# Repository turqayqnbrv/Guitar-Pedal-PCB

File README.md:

# Guitar-Pedal-PCB
This is a project repository for distortion pedal desgined with KiCAD

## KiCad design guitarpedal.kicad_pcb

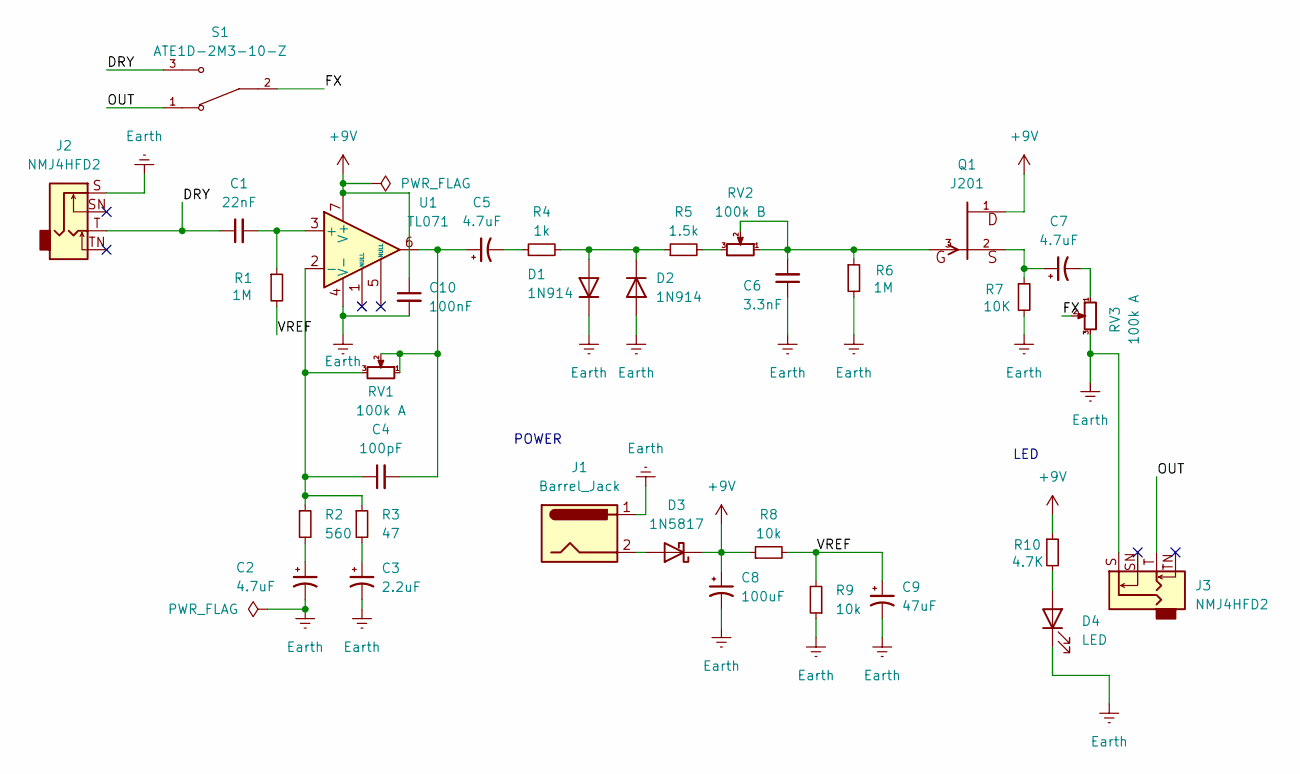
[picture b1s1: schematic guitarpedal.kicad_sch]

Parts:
C1: 22nF; C_Rect_L7.2mm_W2.5mm_P5.00mm_FKS2_FKP2_MKS2_MKP2
C2, C5, C7: 4.7uF; C_Radial_D5.0mm_H7.0mm_P2.00mm
C3: 2.2uF; C_Radial_D5.0mm_H7.0mm_P2.00mm
C4: 100pF; C_Disc_D5.0mm_W2.5mm_P5.00mm
C6: 3.3nF; C_Rect_L7.2mm_W2.5mm_P5.00mm_FKS2_FKP2_MKS2_MKP2
C8: 100uF; C_Radial_D6.3mm_H7.0mm_P2.50mm
C9: 47uF; C_Radial_D5.0mm_H7.0mm_P2.00mm
C10: 100nF; C_Disc_D5.0mm_W2.5mm_P5.00mm
D1, D2: 1N914; D_DO-35_SOD27_P7.62mm_Horizontal
D3: 1N5817; D_DO-41_SOD81_P10.16mm_Horizontal
D4: LED; LED_D5.0mm
J1: Barrel_Jack; BarrelJack_Horizontal
J2, J3: NMJ4HFD2; Jack_6.35mm_Neutrik_NMJ4HFD2_Horizontal
Q1: J201; TO-92L_Inline_Wide; MPN J201
R1, R6: 1M; R_Axial_DIN0207_L6.3mm_D2.5mm_P7.62mm_Horizontal
R2: 560; R_Axial_DIN0207_L6.3mm_D2.5mm_P7.62mm_Horizontal
R3: 47; R_Axial_DIN0207_L6.3mm_D2.5mm_P7.62mm_Horizontal
R4: 1k; R_Axial_DIN0207_L6.3mm_D2.5mm_P7.62mm_Horizontal
R5: 1.5k; R_Axial_DIN0207_L6.3mm_D2.5mm_P7.62mm_Horizontal
R7: 10K; R_Axial_DIN0207_L6.3mm_D2.5mm_P7.62mm_Horizontal
R8, R9: 10k; R_Axial_DIN0207_L6.3mm_D2.5mm_P7.62mm_Horizontal
R10: 4.7K; R_Axial_DIN0207_L6.3mm_D2.5mm_P7.62mm_Horizontal
RV1, RV3: 100k A; Potentiometer_Alps_RK163_Single_Horizontal
RV2: 100k B; Potentiometer_Alps_RK163_Single_Horizontal
S1: ATE1D-2M3-10-Z; SW_ATE1D-2M3-10-Z; MPN ATE1D-2M3-10-Z
U1: TL071; DIP-8_W7.62mm

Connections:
+9V: C8.1, C10.1, D3.1 (K), Q1.1, R8.1, R10.1, U1.7 (V+)
/DRY: C1.1, J2.T, S1.3
/FX: RV3.2, S1.2
/OUT: J3.T, S1.1
/VREF: C9.1, R1.2, R8.2, R9.2
Earth: C2.2, C3.2, C6.1, C8.2, C9.2, C10.2, D1.1 (K), D2.2 (A), D4.1 (K), J1.1, J2.S, J3.S, R6.2, R7.2, R9.1, RV3.3, U1.4 (V-)
unnamed: C2.1, R2.2
unnamed: C3.1, R3.2
unnamed: C4.2, C5.1, RV1.1, RV1.2, U1.6
unnamed: C5.2, R4.1
unnamed: C6.2, Q1.3, R6.1, RV2.1, RV2.2
unnamed: C7.1, Q1.2, R7.1
unnamed: C7.2, RV3.1
unnamed: D1.2 (A), D2.1 (K), R4.2, R5.1
unnamed: D3.2 (A), J1.2
unnamed: D4.2 (A), R10.2
unnamed: R5.2, RV2.3
unnamed: C1.2, R1.1, U1.3 (+)
unnamed: C4.1, R2.1, R3.1, RV1.3, U1.2 (-)

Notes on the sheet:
LED
POWER

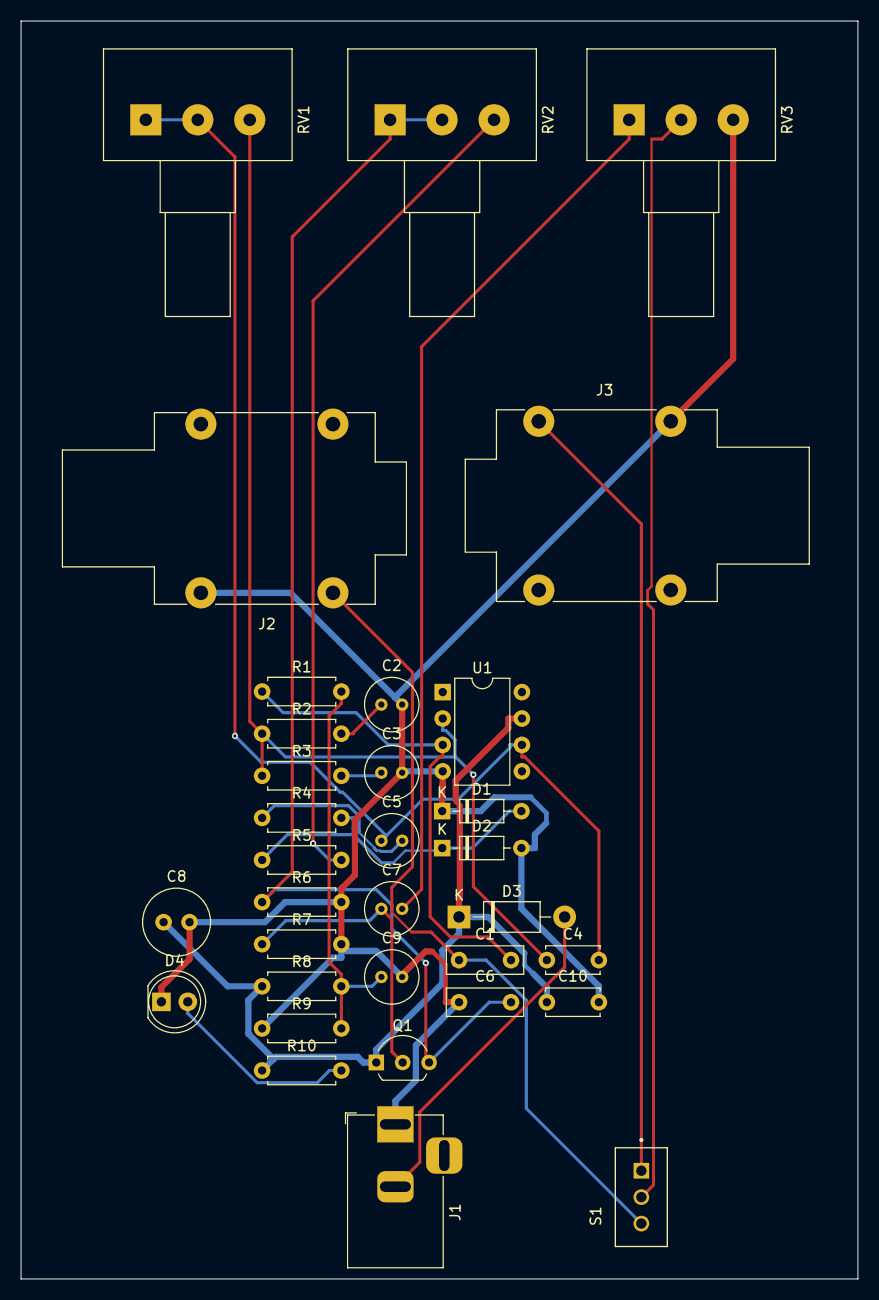
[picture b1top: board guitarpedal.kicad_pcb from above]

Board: 2 copper layers, 80.5 x 121.0 mm, 33 parts (0 on the bottom side), 19 nets.
